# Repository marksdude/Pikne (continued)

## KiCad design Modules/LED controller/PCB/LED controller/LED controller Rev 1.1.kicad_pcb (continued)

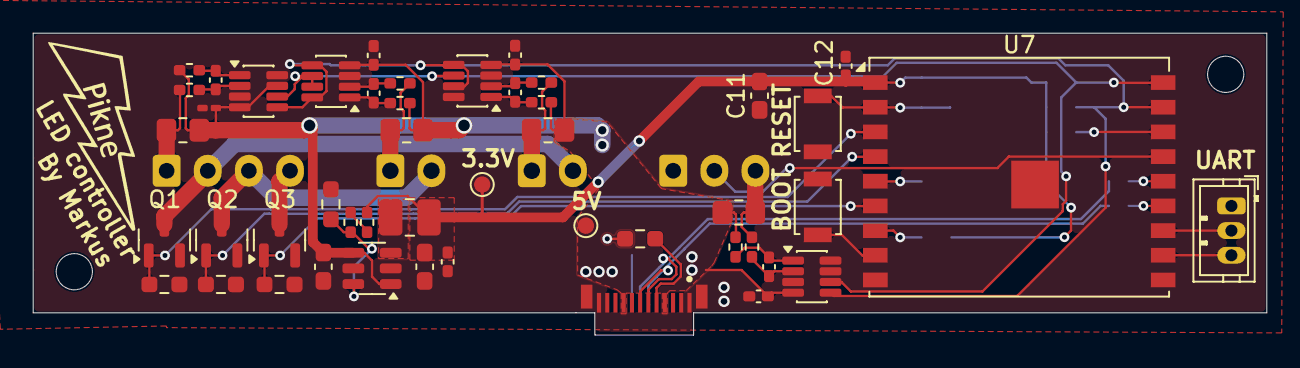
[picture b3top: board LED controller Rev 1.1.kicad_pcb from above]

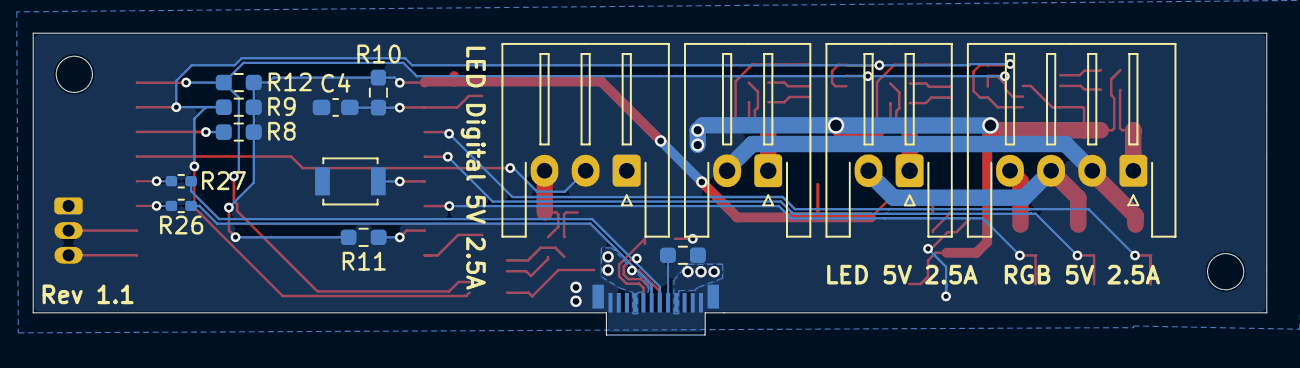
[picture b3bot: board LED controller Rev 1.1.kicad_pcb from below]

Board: 2 copper layers, 75.0 x 18.4 mm, 62 parts (14 on the bottom side), 40 nets.

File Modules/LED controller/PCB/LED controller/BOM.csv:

Id;Designator;Footprint;Quantity;Designation;Price (total) (EUR);Link;Part number
1;C1;C_0603_1608Metric_Pad1.08x0.95mm_HandSolder;1;4.7uf;0,12;https://www.mouser.ee/en/ProductDetail/Samsung-Electro-Mecha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;CL10A475KO8NNNC 
2;C2, C11;C_0603_1608Metric_Pad1.08x0.95mm_HandSolder;2;22uf;0,28;https://www.mouser.ee/en/ProductDetail/Murata-Electronics/GR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;GRM188R60J226MEA0J 
3;C3;C_0402_1005Metric_Pad0.74x0.62mm_HandSolder;1;120pf;0,09;https://www.mouser.ee/en/ProductDetail/Murata-Electronics/GC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;GCM1555C1H121JA16D 
4;C4;C_0603_1608Metric_Pad1.08x0.95mm_HandSolder;1;1uf;0,09;https://www.mouser.ee/en/ProductDetail/Samsung-Electro-Mecha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;CL10B105KQ8NNNC 
5;C5, C6, C7, C9, C10, C12, C13, C14;C_0402_1005Metric_Pad0.74x0.62mm_HandSolder;8;100nF;0,15;https://www.mouser.ee/en/ProductDetail/Murata-Electronics/GR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;GRM155R62A104ME14D 
6;C8;C_0201_0603Metric_Pad0.64x0.40mm_HandSolder;1;100nF;0,09;https://www.mouser.ee/en/ProductDetail/Murata-Electronics/GR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;GRM033R61C104KE18J 
7;;;;;;;
8;J1, J2;JST_XH_S2B-XH-A-1_1x02_P2.50mm_Horizontal;2;LED;0,26;https://www.mouser.ee/en/ProductDetail/JST-Commercial/S2B-XH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;S2B-XH-A-1(LF)(SN) 
9;J3;SAMESKY_UP32-1-C-H-G-BMT-P24;1;UP32-1-C-H-G-BMT-P24;0,78;https://www.mouser.ee/en/ProductDetail/Same-Sky/UP32-1-C-H-G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;UP32-1-C-H-G-BMT-P24 
10;J4;JST_XH_S4B-XH-A-1_1x04_P2.50mm_Horizontal;1;RGB 2A max;0,6;https://www.mouser.ee/ProductDetail/JST-Commercial/S4B-XH-SM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;S4B-XH-SM4-TB(LF)(SN) 
11;J5;JST_XH_S3B-XH-A-1_1x03_P2.50mm_Horizontal;1;RGB 2A max;0,13;https://www.mouser.ee/ProductDetail/JST-Commercial/S3B-XH-A-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;S3B-XH-A-1(LF)(SN) 
12;J7;JST_ZH_B3B-ZR_1x03_P1.50mm_Vertical;1;UART;0,21;https://www.mouser.ee/en/ProductDetail/JST-Commercial/B3B-ZR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;B3B-ZR-3.4(LF)(SN) 
13;L1;L_1008_2520Metric_Pad1.43x2.20mm_HandSolder;1;1uH;0,22;https://www.mouser.ee/ProductDetail/TDK/VLS252012HBX-1R0M-1?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;VLS252012HBX-1R0M-1 
14;Q1, Q2, Q3;SOT-23;3;AO3400A;0,38;https://www.lcsc.com/product-detail/C20917.html;AO3400A
15;R1;R_0402_1005Metric_Pad0.72x0.64mm_HandSolder;1;300k;0,08;https://www.mouser.ee/en/ProductDetail/YAGEO/AC0402FR-07300K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;AC0402FR-07300KL 
16;R2, R6, R7, R8, R10, R11;R_0603_1608Metric_Pad0.98x0.95mm_HandSolder;6;10k;0,09;https://www.mouser.ee/en/ProductDetail/YAGEO/RT0603FRE1310KL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;RT0603FRE1310KL 
17;R3;R_0603_1608Metric_Pad0.98x0.95mm_HandSolder;1;100k;0,09;https://www.mouser.ee/en/ProductDetail/YAGEO/RC0603FR-10100K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;RC0603FR-10100KL 
18;R4, R5;R_0603_1608Metric_Pad0.98x0.95mm_HandSolder;2;5.1k;0,09;https://www.mouser.ee/en/ProductDetail/YAGEO/AC0603JR-075K1L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;AC0603JR-075K1L 
19;R9, R12;R_0603_1608Metric_Pad0.98x0.95mm_HandSolder;2;4.7k;0,09;https://www.mouser.ee/en/ProductDetail/YAGEO/AC0603JR-074K7L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;AC0603JR-074K7L 
20;R13, R14, R17, R18, R20, R21, R23, R24;R_0402_1005Metric_Pad0.72x0.64mm_HandSolder;8;10 Ohm;0,08;https://www.mouser.ee/en/ProductDetail/Bourns/CR0402-FX-10R0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;CR0402-FX-10R0GLF 
21;R15, R16, R19, R22;R_0805_2012Metric_Pad1.20x1.40mm_HandSolder;4;20m;1,17;https://www.mouser.ee/en/ProductDetail/Eaton-Electronics/MFS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;MFSA0805R0200FIM 
22;R25;R_0402_1005Metric_Pad0.72x0.64mm_HandSolder;1;150k;0,09;https://www.mouser.ee/en/ProductDetail/YAGEO/RC0402FR-07150K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;RC0402FR-07150KP 
23;R26, R27;R_0402_1005Metric_Pad0.72x0.64mm_HandSolder;2;22 Ohm;0,08;https://www.mouser.ee/en/ProductDetail/Bourns/CR0402-FX-22R0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;CR0402-FX-22R0GLF 
24;SW1, SW2, SW3;SW_SPST_B3U-1000P;3;;2,81;https://www.mouser.ee/en/ProductDetail/Omron-Electronics/B3U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;B3U-1000P 
25;;;;;;;
26;;;;;;;
27;TP1;TestPoint_Pad_D1.0mm;1;3.3V;;;
28;TP2;TestPoint_Pad_D1.0mm;1;5V;;;
29;U1, U2, U3, U5;SOT-23-8;4;INA219AxDCN;7,28;https://www.mouser.ee/ProductDetail/Texas-Instruments/INA219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;INA219AIDCNR 
30;U4;SOT-23-6;1;TPS62A02APDDC;0,21;https://www.mouser.ee/ProductDetail/Texas-Instruments/TPS62A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;TPS62A02APDDCR 
31;U7;ESP32-C3-WROOM-02U;1;ESP32-C3-WROOM-02;3,19;https://www.mouser.ee/en/ProductDetail/Espressif-Systems/ESP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;ESP32-C3-WROOM-02U-N4 
;;;;Total (EUR);18,75;;
;;;;Total (USD);21,75;;

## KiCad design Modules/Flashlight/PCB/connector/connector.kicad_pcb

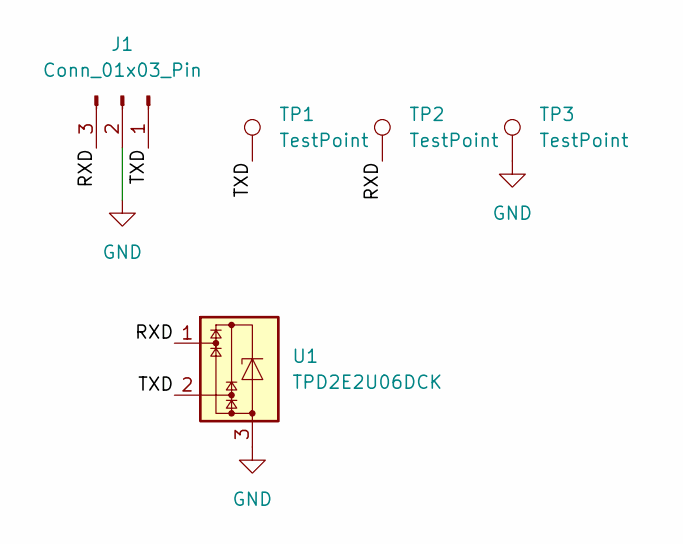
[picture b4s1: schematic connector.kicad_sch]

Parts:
J1: Conn_01x03_Pin; Pogo 3 Pin
TP1, TP2, TP3: TestPoint; TestPoint_Pad_D1.0mm
U1: TPD2E2U06DCK; SOT-323_SC-70

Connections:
/RXD: J1.3, TP2.1 (1_1), U1.1
/TXD: J1.1, TP1.1 (1_1), U1.2
GND: J1.2, TP3.1 (1_1), U1.3

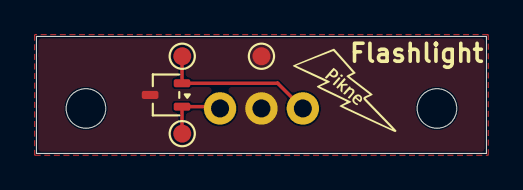
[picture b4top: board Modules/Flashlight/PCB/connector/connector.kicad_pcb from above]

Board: 2 copper layers, 25.0 x 6.5 mm, 5 parts (1 on the bottom side), 3 nets.

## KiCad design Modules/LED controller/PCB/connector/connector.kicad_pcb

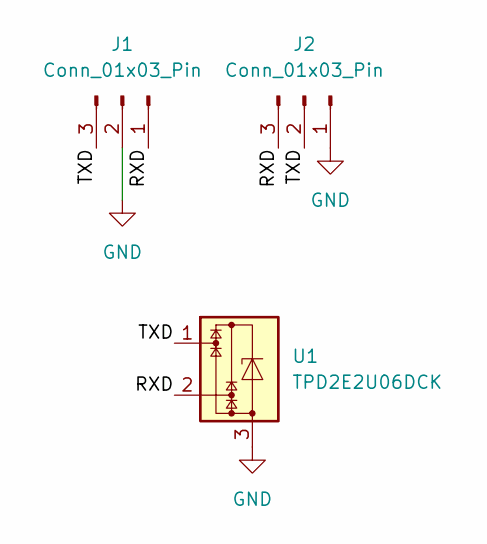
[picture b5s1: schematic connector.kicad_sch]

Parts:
J1: Conn_01x03_Pin; Pogo 3 Pin
J2: Conn_01x03_Pin; JST_ZH_S3B-ZR-SM4A-TF_1x03-1MP_P1.50mm_Horizontal
U1: TPD2E2U06DCK; SOT-323_SC-70

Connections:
/RXD: J1.1, J2.3, U1.2
/TXD: J1.3, J2.2, U1.1
GND: J1.2, J2.1, U1.3

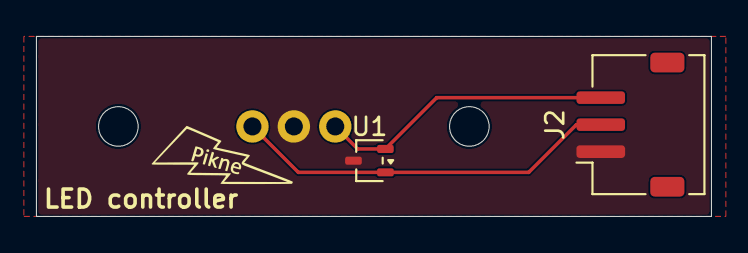
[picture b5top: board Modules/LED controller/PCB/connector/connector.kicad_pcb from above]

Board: 2 copper layers, 37.5 x 10.0 mm, 3 parts (1 on the bottom side), 3 nets.

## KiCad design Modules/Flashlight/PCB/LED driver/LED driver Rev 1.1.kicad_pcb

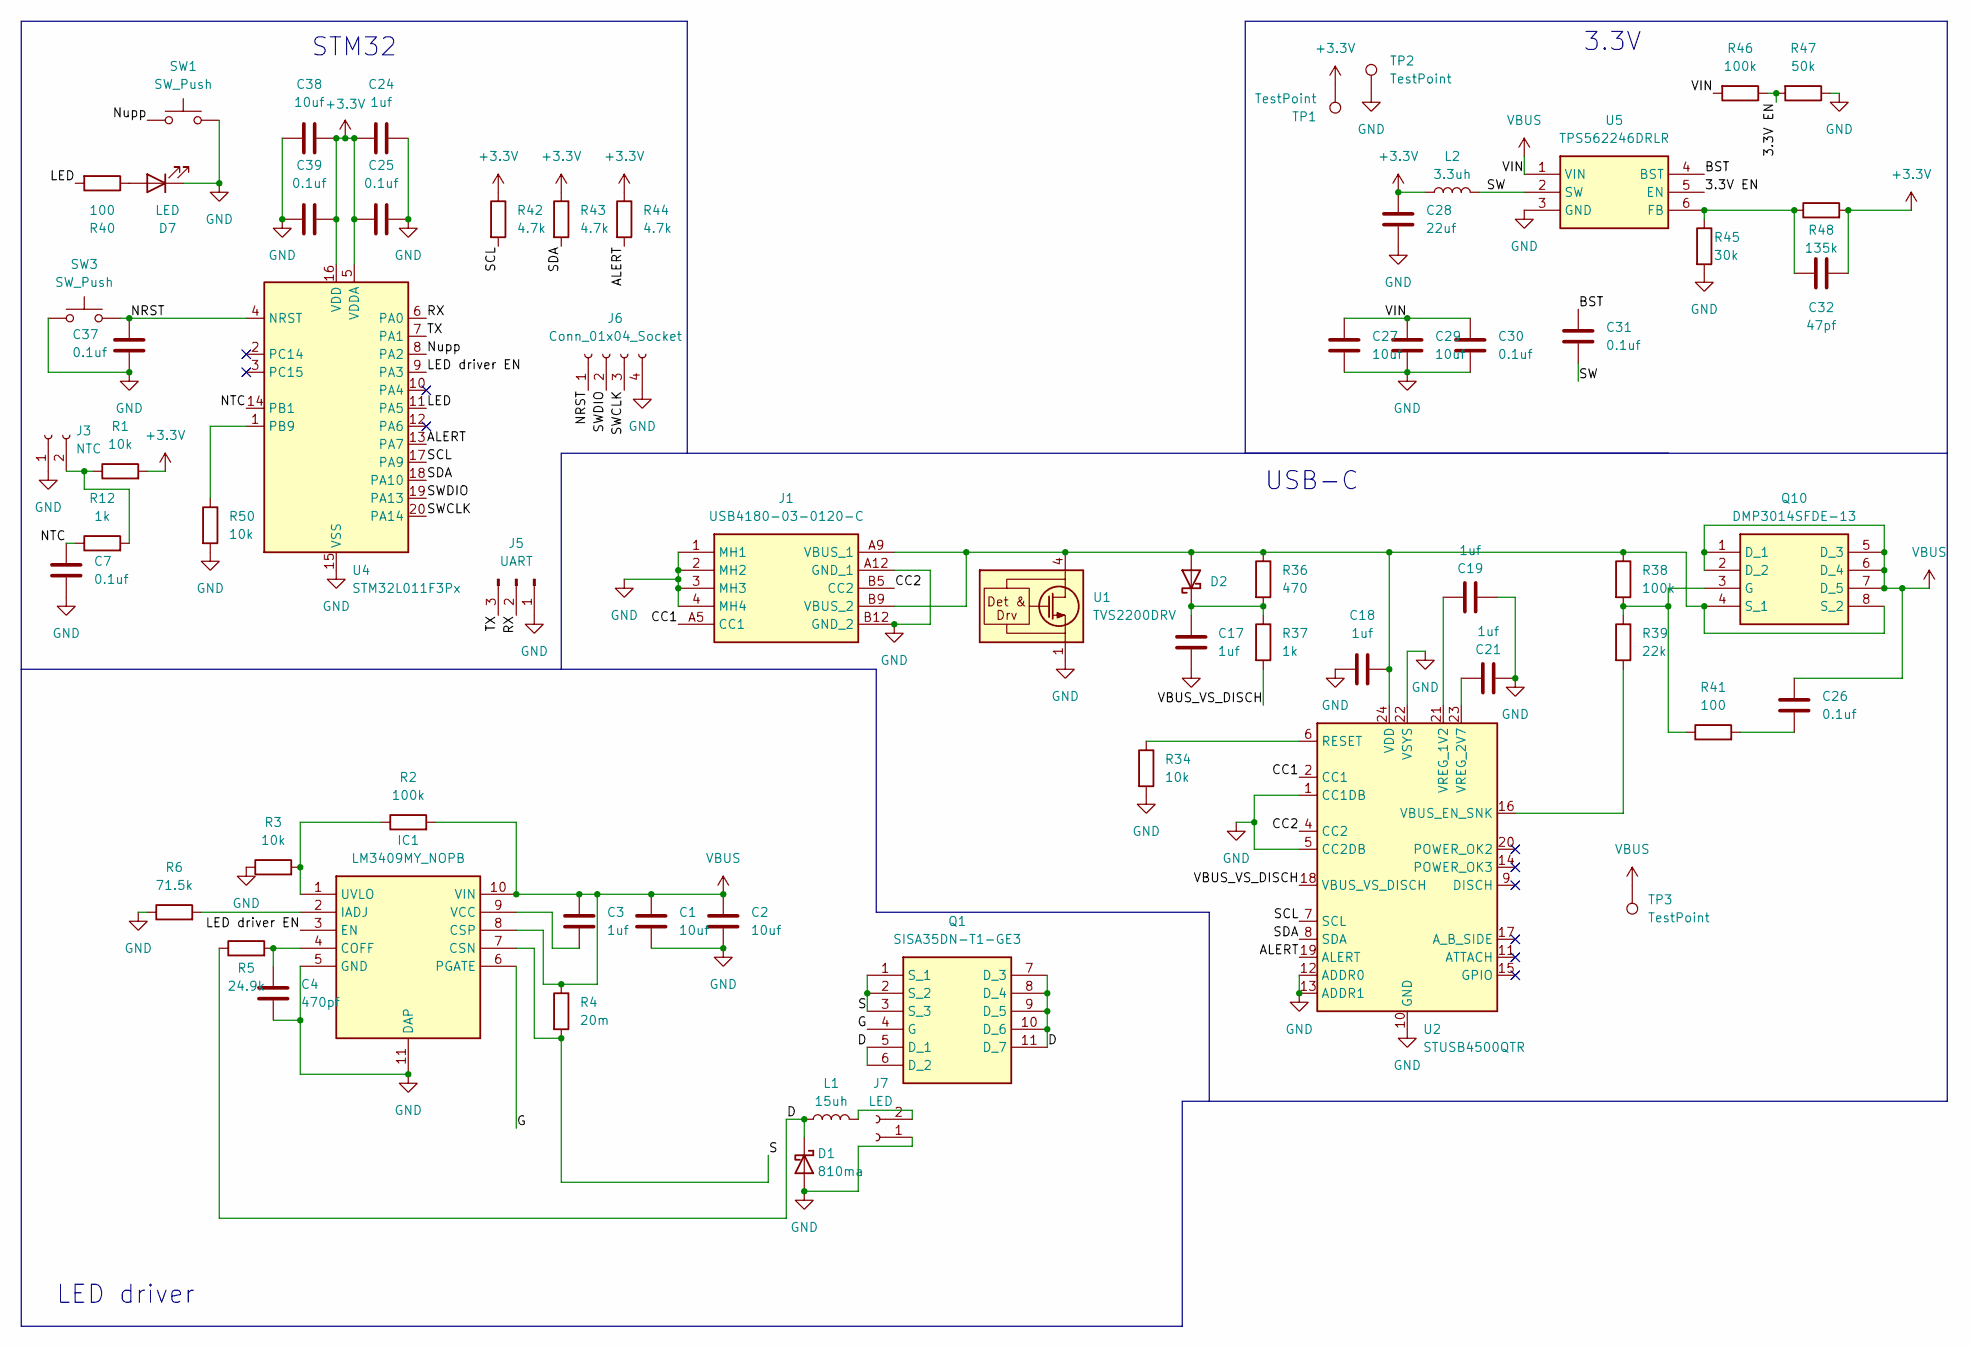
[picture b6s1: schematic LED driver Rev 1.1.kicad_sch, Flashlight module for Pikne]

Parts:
C1, C2: 10uf; C_1206_3216Metric
C3, C19, C21: 1uf; C_0402_1005Metric
C4: 470pf; C_0402_1005Metric
C7, C25, C26, C30, C31, C37, C39: 0.1uf; C_0402_1005Metric
C17, C18, C24: 1uf; C_0603_1608Metric
C27, C29, C38: 10uf; C_0603_1608Metric
C28: 22uf; C_0805_2012Metric
C32: 47pf; R_0402_1005Metric
D1: 810ma; D_SMF
D2: D_Schottky; D_SOD-323_HandSoldering
D7: LED; LED_0603_1608Metric
IC1: LM3409MY_NOPB; SOP50P490X109-11N; Mouser Part Number 926-LM3409MY/NOPB
J1: USB4180-03-0120-C; USB4180030120C; Mouser Part Number 640-USB4180-03-0120C
J3: NTC; JST_ZH_B2B-ZR_1x02_P1.50mm_Vertical
J5: UART; JST_ZH_B3B-ZR_1x03_P1.50mm_Vertical
J6: Conn_01x04_Socket; JST_ZH_B4B-ZR_1x04_P1.50mm_Vertical
J7: LED; JST_XH_S2B-XH-A-1_1x02_P2.50mm_Horizontal
L1: 15uh; L_Bourns_SRP1038C_10.0x10.0mm
L2: 3.3uh; INDC3225X120N
Q1: SISA35DN-T1-GE3; SISA35DNT1GE3; Mouser Part Number 78-SISA35DN-T1-GE3
Q10: DMP3014SFDE-13; DMP1022UFDEQ7; Manufacturer_Part_Number DMP3014SFDE-13
R1, R3, R34: 10k; R_0603_1608Metric
R2, R38: 100k; R_0603_1608Metric
R4: 20m; R_1206_3216Metric
R5: 24.9k; R_0603_1608Metric
R6: 71.5k; R_0603_1608Metric
R12: 1k; R_0402_1005Metric
R36: 470; R_0603_1608Metric
R37: 1k; R_0603_1608Metric
R39: 22k; R_0603_1608Metric
R40, R41: 100; R_0402_1005Metric
R42, R43, R44: 4.7k; R_0603_1608Metric
R45: 30k; R_0402_1005Metric
R46: 100k; R_0402_1005Metric
R47: 50k; R_0402_1005Metric
R48: 135k; R_0402_1005Metric
R50: 10k; R_0402_1005Metric
SW1: SW_Push; SW_Tactile_SPST_Angled_PTS645Vx39-2LFS
SW3: SW_Push; SW_SPST_B3U-1000P
TP1, TP2, TP3: TestPoint; TestPoint_Pad_D1.0mm
U1: TVS2200DRV; WSON-6-1EP_2x2mm_P0.65mm_EP1x1.6mm
U2: STUSB4500QTR; QFN-24-1EP_4x4mm_P0.5mm_EP2.7x2.7mm
U4: STM32L011F3Px; TSSOP-20_4.4x6.5mm_P0.65mm
U5: TPS562246DRLR; SOTFL50P160X60-6N; Mouser Part Number 595-TPS562246DRLR

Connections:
+3.3V: C24.1, C25.1, C28.1, C32.1, C38.2, C39.2, L2.1, R1.2, R42.1, R43.1, R44.1, R48.2, TP1.1 (1_1), U4.5 (VDDA), U4.16 (VDD)
/3.3V EN: R46.1, R47.2, U5.5 (EN)
/ALERT: R44.2, U2.19 (ALERT), U4.13 (PA7)
/BST: C31.2, U5.4 (BST)
/CC1: J1.A5 (CC1), U2.2 (CC1)
/CC2: J1.B5 (CC2), U2.4 (CC2)
/D: D1.1 (K), L1.1, Q1.5 (D_1), Q1.6 (D_2), Q1.7 (D_3), Q1.8 (D_4), Q1.9 (D_5), Q1.10 (D_6), Q1.11 (D_7), R5.1
/G: IC1.6 (PGATE), Q1.4 (G)
/LED: R40.2, U4.11 (PA5)
/LED driver EN: IC1.3 (EN), U4.9 (PA3)
/NRST: C37.2, J6.1, SW3.2, U4.4 (NRST)
/NTC: C7.1, R12.1, U4.14 (PB1)
/Nupp: SW1.1, U4.8 (PA2)
/RX: J5.2, U4.6 (PA0)
/S: IC1.7 (CSN), Q1.1 (S_1), Q1.2 (S_2), Q1.3 (S_3), R4.2
/SCL: R42.2, U2.7 (SCL), U4.17 (PA9)
/SDA: R43.2, U2.8 (SDA), U4.18 (PA10)
/SW: C31.1, L2.2, U5.2 (SW)
/SWCLK: J6.3, U4.20 (PA14)
/SWDIO: J6.2, U4.19 (PA13)
/TX: J5.3, U4.7 (PA1)
/VBUS_VS_DISCH: R37.2, U2.18 (VBUS_VS_DISCH)
GND: C1.2, C2.2, C4.2, C7.2, C17.1, C18.1, C19.1, C21.1, C24.2, C25.2, C27.2, C28.2, C29.2, C30.2, C37.1, C38.1, C39.1, D1.2 (A), D7.1 (K), IC1.5 (GND), IC1.11 (DAP), J1.1 (MH1), J1.2 (MH2), J1.3 (MH3), J1.4 (MH4), J1.A12 (GND_1), J1.B12 (GND_2), J3.1, J5.1, J6.4, J7.1, R3.1, R6.1, R34.2, R45.2, R47.1, R50.2, SW1.2, SW3.1, TP2.1 (1_1), U1.1 (GND), U1.2 (GND), U1.3 (GND), U1.7 (GND), U2.1 (CC1DB), U2.5 (CC2DB), U2.10 (GND), U2.12 (ADDR0), U2.13 (ADDR1), U2.22 (VSYS), U2.25 (GND), U4.15 (VSS), U5.3 (GND)
unnamed: C26.2, R41.2
unnamed: C18.2, D2.2 (A), J1.A9 (VBUS_1), J1.B9 (VBUS_2), Q10.4 (S_1), Q10.8 (S_2), R36.1, R38.1, U1.4 (IN), U1.5 (IN), U1.6 (IN), U2.24 (VDD)
unnamed: C17.2, D2.1 (K), R36.2, R37.1
unnamed: D7.2 (A), R40.1
unnamed: C4.1, IC1.4 (COFF), R5.2
unnamed: IC1.2 (IADJ), R6.2
unnamed: IC1.1 (UVLO), R2.1, R3.2
unnamed: C3.2, IC1.9 (VCC)
unnamed: J3.2, R1.1, R12.2
unnamed: J7.2, L1.2
unnamed: Q10.3 (G), R38.2, R39.1, R41.1
unnamed: R34.1, U2.6 (RESET)
unnamed: R39.2, U2.16 (VBUS_EN_SNK)
unnamed: C19.2, U2.21 (VREG_1V2)
unnamed: C21.2, U2.23 (VREG_2V7)
unnamed: R50.1, U4.1 (PB9)
unnamed: C32.2, R45.1, R48.1, U5.6 (FB)
VBUS: C1.1, C2.1, C3.1, C26.1, C27.1, C29.1, C30.1, IC1.8 (CSP), IC1.10 (VIN), Q10.1 (D_1), Q10.2 (D_2), Q10.5 (D_3), Q10.6 (D_4), Q10.7 (D_5), R2.2, R4.1, R46.2, TP3.1 (1_1), U5.1 (VIN)

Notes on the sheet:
3.3V
LED driver
USB-C
STM32

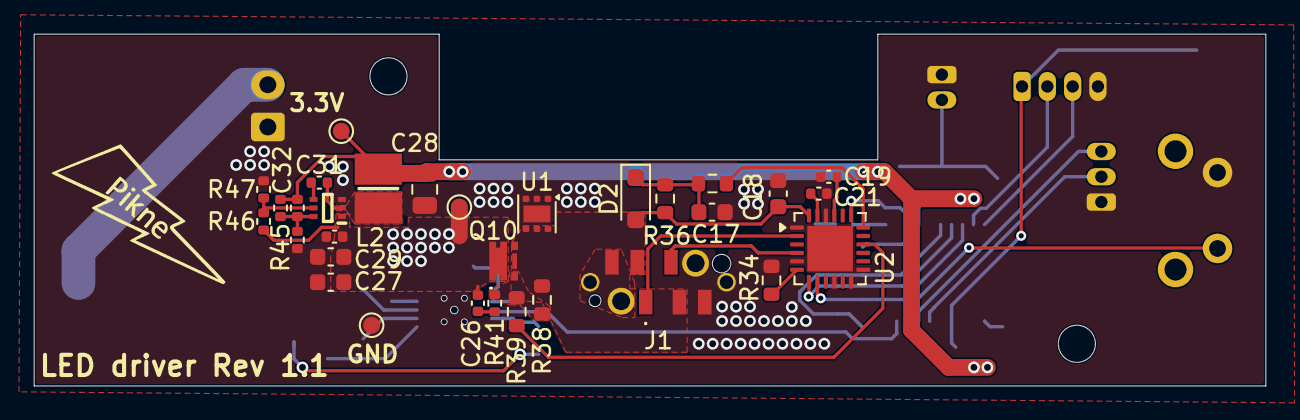
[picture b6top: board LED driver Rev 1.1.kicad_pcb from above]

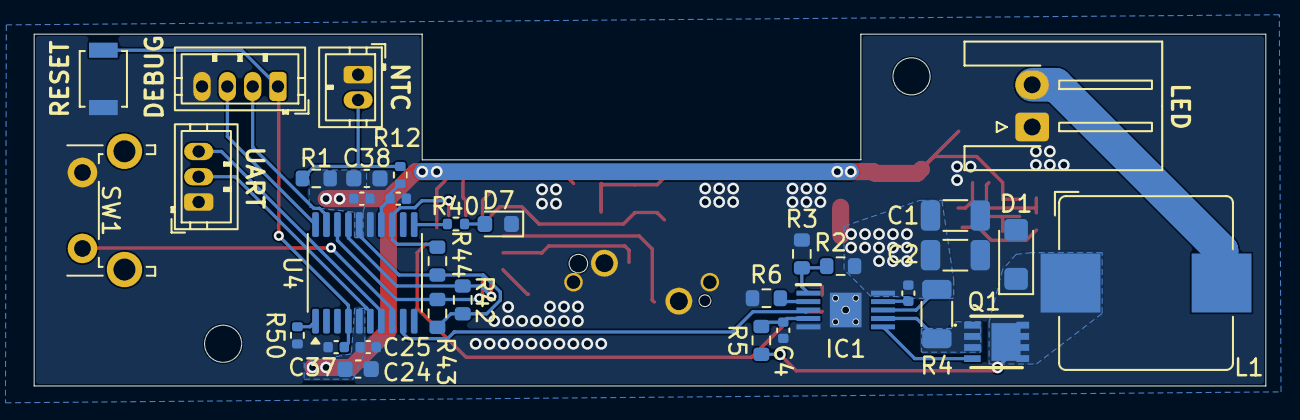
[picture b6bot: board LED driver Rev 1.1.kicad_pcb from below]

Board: 2 copper layers, 73.0 x 20.8 mm, 65 parts (34 on the bottom side), 41 nets.

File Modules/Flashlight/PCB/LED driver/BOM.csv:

Id;Designator;Footprint;Quantity;Designation;Price (total) (EUR);Link;Part number;alternative
1;C1, C2, C27, C29;C_1206_3216Metric;4;10uf;1;https://www.mouser.ee/en/ProductDetail/TAIYO-YUDEN/MSAST31LS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;MSAST31LSB5106KTNA01 ;
2;C3, C19, C21;C_0402_1005Metric;3;1uf;0,26;https://www.mouser.ee/en/ProductDetail/Murata-Electronics/GR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;GRM155R61E105MA12D ;
3;C4;C_0402_1005Metric;1;470pf;0,09;https://www.mouser.ee/en/ProductDetail/Murata-Electronics/GC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;GCM155L81H471KA37D ;
4;C5;C_0603_1608Metric;1;4.7uf;0,27;https://www.mouser.ee/en/ProductDetail/Murata-Electronics/GR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;GRM188R6YA475ME15D ;
5;C7, C25, C26, C30, C31, C37, C39;C_0402_1005Metric;7;0.1uf;0,15;https://www.mouser.ee/en/ProductDetail/Murata-Electronics/GR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;GRM155R62A104ME14D ;
6;C17, C18, C24;C_0603_1608Metric;3;1uf;0,19;https://www.mouser.ee/en/ProductDetail/Samsung-Electro-Mecha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;CL10A105KA8NNND ;
7;C38;C_0603_1608Metric;1;10uf;0,09;https://www.mouser.ee/en/ProductDetail/Samsung-Electro-Mecha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;CL10A105KA8NFNC ;
8;C28;C_0805_2012Metric;1;22uf;0,15;https://www.mouser.ee/en/ProductDetail/Samsung-Electro-Mecha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;CL21A226MQQNNNE ;
9;C32;R_0402_1005Metric;1;47pf;0,09;https://www.mouser.ee/en/ProductDetail/Murata-Electronics/GR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;GRM1555C1H470GA01D ;
10;D1;D_SMF;1;1.2A;0,4;https://www.mouser.ee/en/ProductDetail/Vishay-Semiconductors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;V3FL45-M3/H ;
11;D2;D_SOD-323_HandSoldering;1;D_Schottky;0,13;https://www.mouser.ee/en/ProductDetail/onsemi/NSR0530HT1G?qs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;NSR0530HT1G ;
12;D3;SOT-323_SC-70;1;ESDA25W;0,36;https://www.mouser.ee/en/ProductDetail/STMicroelectronics/ES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;ESDA25W ;
13;D7;LED_0603_1608Metric;1;LED;0,28;https://www.mouser.ee/en/ProductDetail/ams-OSRAM/KT-EELP41.1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;KT EELP41.12-S2U1-25-2X4X-5-R18 ;
14;IC1;SOP50P490X109-11N;1;LM3409MY_NOPB;2,41;https://www.mouser.ee/en/ProductDetail/Texas-Instruments/LM3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;LM3409HVMYX/NOPB ;
15;J1;USB4180030120C;1;USB4180-03-0120-C;0,87;https://www.mouser.ee/en/ProductDetail/GCT/USB4180-03-0120-C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;USB4180-03-0120-C ;
16;J3;JST_ZH_B2B-ZR_1x02_P1.50mm_Vertical;1;NTC;0,1;https://www.mouser.ee/en/ProductDetail/JST-Commercial/B2B-ZR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;B2B-ZR(LF)(SN) ;
17;J5;JST_ZH_B3B-ZR_1x03_P1.50mm_Vertical;1;UART;0,21;https://www.mouser.ee/en/ProductDetail/JST-Commercial/B3B-ZR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;B3B-ZR-3.4(LF)(SN) ;
18;J6;JST_ZH_B4B-ZR_1x04_P1.50mm_Vertical;1;Conn_01x04_Socket;0,21;https://www.mouser.ee/en/ProductDetail/JST-Commercial/B4B-ZR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;B4B-ZR-3.4(LF)(SN) ;
19;J7;JST_XH_S2B-XH-A-1_1x02_P2.50mm_Horizontal;1;LED;0,13;https://www.mouser.ee/en/ProductDetail/JST-Commercial/S2B-XH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;S2B-XH-A-1(LF)(SN) ;
20;L1;L_Bourns_SRP1038C_10.0x10.0mm;1;15uh;0,84;https://www.mouser.ee/en/ProductDetail/Bourns/SRP1038CC-150M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;SRP1038CC-150M ;SRP1038C-150M 
21;L2;INDC3225X120N;1;3.3uh;0,34;https://www.mouser.ee/en/ProductDetail/Bourns/SRP3212A-3R3M?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;SRP3212A-3R3M ;
22;Q1;SISA35DNT1GE3;1;SISA35DN-T1-GE3;0,67;https://www.mouser.ee/en/ProductDetail/Vishay-Semiconductors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;SISA35DN-T1-GE3 ;
23;Q10;DMP1022UFDEQ7;1;DMP3014SFDE-13;0,43;https://www.mouser.ee/en/ProductDetail/Diodes-Incorporated/D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;DMP3014SFDE-13 ;
24;R1, R3;R_0603_1608Metric;2;10k;0,09;https://www.mouser.ee/en/ProductDetail/YAGEO/RT0603FRE1310KL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;RT0603FRE1310KL ;
25;R2, R38;R_0603_1608Metric;2;100k;0,12;https://www.mouser.ee/en/ProductDetail/YAGEO/RC0603FR-10100K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;RC0603FR-10100KL ;
26;R4;R_1206_3216Metric;1;20m;0,32;https://www.mouser.ee/en/ProductDetail/Eaton-Electronics/MFS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;MFSA1206R0200FCM ;
27;R5;R_0603_1608Metric;1;24.9k;0,09;https://www.mouser.ee/en/ProductDetail/SEI-Stackpole/RNCP060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;RNCP0603FTD24K9 ;
28;R6;R_0603_1608Metric;1;71.5k;0,09;https://www.mouser.ee/en/ProductDetail/Vishay/CRCW060371K5FK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;CRCW060371K5FKEA ;
29;R7, R9, R46;R_0402_1005Metric;3;100k;0,09;https://www.mouser.ee/en/ProductDetail/YAGEO/RC0402FR-07100K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;RC0402FR-07100KL ;
30;R12;R_0402_1005Metric;1;1k;0,09;https://www.mouser.ee/en/ProductDetail/YAGEO/RC0402FR-101KL?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;RC0402FR-101KL ;
31;R34, R50;R_0402_1005Metric;2;10k;0,09;https://www.mouser.ee/en/ProductDetail/YAGEO/RC0402FR-0710KL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;RC0402FR-0710KL ;
32;R36;R_0603_1608Metric;1;470;0,09;https://www.mouser.ee/en/ProductDetail/YAGEO/RC0603JR-07470R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;RC0603JR-07470RL ;
33;R37;R_0603_1608Metric;1;1k;0,09;https://www.mouser.ee/en/ProductDetail/YAGEO/AC0603JR-131KL?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;AC0603JR-131KL ;
34;R39;R_0603_1608Metric;1;22k;0,09;https://www.mouser.ee/en/ProductDetail/Walsin/WR06X223-JTL?q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;WR06X223 JTL ;
35;R41;R_0402_1005Metric;1;100;0,08;https://www.mouser.ee/en/ProductDetail/YAGEO/AC0402FR-13100R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;AC0402FR-13100RL ;
36;R42, R43, R44;R_0603_1608Metric;3;4.7k;0,09;https://www.mouser.ee/en/ProductDetail/YAGEO/AC0603JR-074K7L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;AC0603JR-074K7L ;
37;R45;R_0402_1005Metric;1;30k;0,08;https://www.mouser.ee/en/ProductDetail/Walsin/WR04X3002FTL?q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;WR04X3002FTL ;
38;R47;R_0402_1005Metric;1;50k;0,09;https://www.mouser.ee/en/ProductDetail/SEI-Stackpole/RNCF040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;RNCF0402DKE50K0 ;
39;R48;R_0402_1005Metric;1;135k;0,15;https://www.mouser.ee/en/ProductDetail/KOA-Speer/RN73H1ETTP1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;RN73H1ETTP1353F50 ;
40;SW1;SW_Tactile_SPST_Angled_PTS645Vx39-2LFS;1;SW_Push;0,3;https://www.mouser.ee/en/ProductDetail/CK/PTS645VM39-2-LFS?q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;PTS645VM39-2 LFS ;
41;SW3;SW_SPST_B3U-1000P;1;SW_Push;0,94;https://www.mouser.ee/en/ProductDetail/Omron-Electronics/B3U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;B3U-1000P ;
42;TP1, TP2, TP3;TestPoint_Pad_D1.0mm;3;TestPoint;;;;
43;U1;WSON-6-1EP_2x2mm_P0.65mm_EP1x1.6mm;1;TVS2200DRV;0,93;https://www.mouser.ee/en/ProductDetail/Texas-Instruments/TVS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;TVS2200DRVR ;
44;U2;QFN-24-1EP_4x4mm_P0.5mm_EP2.7x2.7mm;1;STUSB4500QTR;0,91;https://www.mouser.ee/en/ProductDetail/STMicroelectronics/ST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;STUSB4500QTR ;
45;U4;TSSOP-20_4.4x6.5mm_P0.65mm;1;STM32L011F3Px;1,58;https://www.mouser.ee/en/ProductDetail/STMicroelectronics/ST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;STM32L011F3P6 ;
46;U5;SOTFL50P160X60-6N;1;TPS562246DRLR;0,27;https://www.mouser.ee/en/ProductDetail/Texas-Instruments/TPS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;TPS562246DRLR ;
47;R40;R_0402_1005Metric;1;160;0,07;https://www.mouser.ee/en/ProductDetail/YAGEO/RC0402JR-07160R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;RC0402JR-07160RL ;
;;;;Total (EUR);16,41;;;
;;;;Total (USD);19,04;;;

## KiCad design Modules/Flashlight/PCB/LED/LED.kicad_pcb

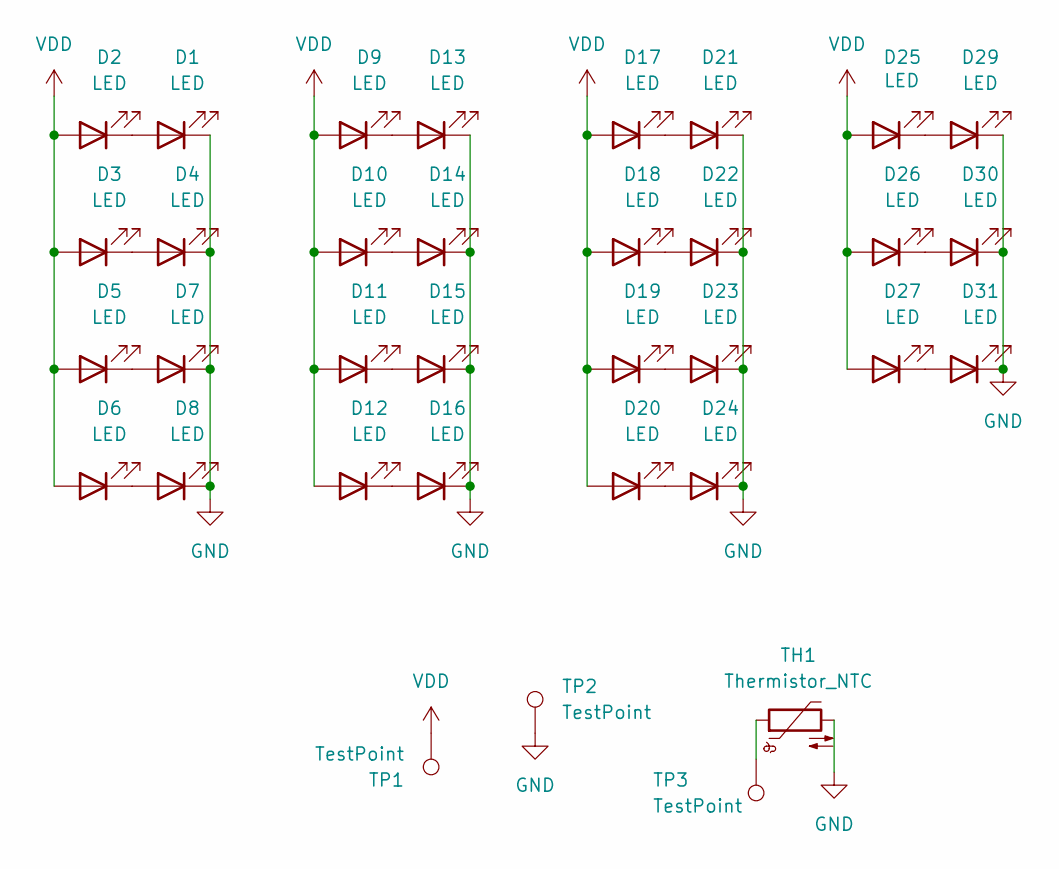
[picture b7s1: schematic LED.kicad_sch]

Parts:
D1, D2, D3, D4, D5, D6, D7, D8, D9, D10, D11, D12, D13, D14, D15, D16, D17, D18, D19, D20, D21, D22, D23, D24, D25, D26, D27, D29, D30, D31: LED; Q9LR37
TH1: Thermistor_NTC; R_0402_1005Metric
TP1, TP2: TestPoint; TestPoint_Pad_D3.0mm
TP3: TestPoint; TestPoint_Pad_D1.5mm

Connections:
GND: D1.1 (K), D4.1 (K), D7.1 (K), D8.1 (K), D13.1 (K), D14.1 (K), D15.1 (K), D16.1 (K), D21.1 (K), D22.1 (K), D23.1 (K), D24.1 (K), D29.1 (K), D30.1 (K), D31.1 (K), TH1.2, TP2.1 (1_1)
unnamed: D1.2 (A), D2.1 (K)
unnamed: D3.1 (K), D4.2 (A)
unnamed: D5.1 (K), D7.2 (A)
unnamed: D6.1 (K), D8.2 (A)
unnamed: D10.1 (K), D14.2 (A)
unnamed: D11.1 (K), D15.2 (A)
unnamed: D12.1 (K), D16.2 (A)
unnamed: D9.1 (K), D13.2 (A)
unnamed: D17.1 (K), D21.2 (A)
unnamed: D18.1 (K), D22.2 (A)
unnamed: D19.1 (K), D23.2 (A)
unnamed: D20.1 (K), D24.2 (A)
unnamed: D25.1 (K), D29.2 (A)
unnamed: D26.1 (K), D30.2 (A)
unnamed: D27.1 (K), D31.2 (A)
unnamed: TH1.1, TP3.1 (1_1)
VDD: D2.2 (A), D3.2 (A), D5.2 (A), D6.2 (A), D9.2 (A), D10.2 (A), D11.2 (A), D12.2 (A), D17.2 (A), D18.2 (A), D19.2 (A), D20.2 (A), D25.2 (A), D26.2 (A), D27.2 (A), TP1.1 (1_1)

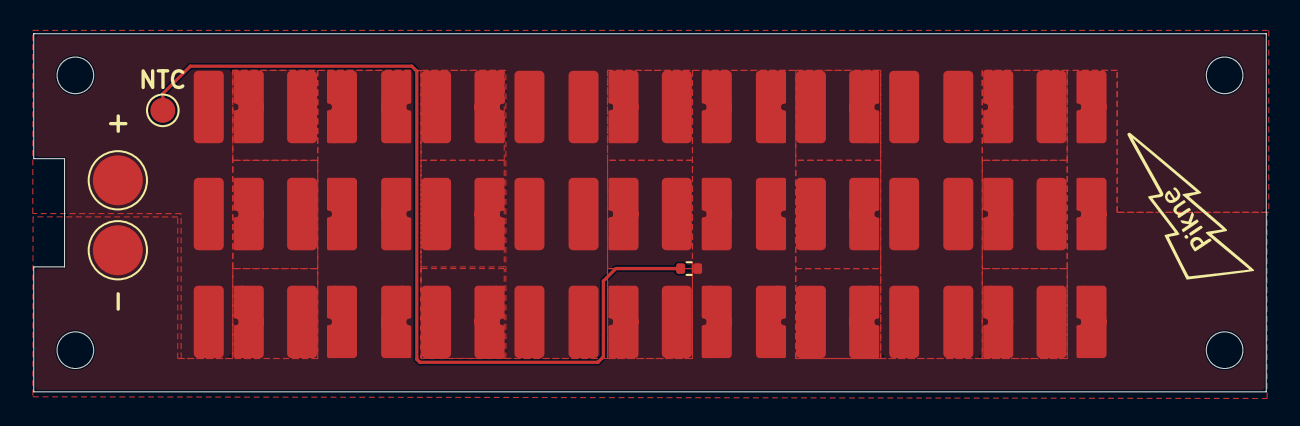
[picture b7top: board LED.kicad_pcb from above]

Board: 2 copper layers, 74.0 x 21.5 mm, 34 parts (0 on the bottom side), 18 nets.

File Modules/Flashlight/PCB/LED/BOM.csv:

Id;Designator;Footprint;Quantity;Designation;Price (total) (EUR);Link;Part number
1;D1, D2, D3, D4, D5, D6, D7, D8, D9, D10, D11, D12, D13, D14, D15, D16, D17, D18, D19, D20, D21, D22, D23, D24, D25, D26, D27, D29, D30, D31;Q9LR37;30;LED;23,22;https://www.mouser.ee/en/ProductDetail/ams-OSRAM/GW-Q9LR37EM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;GW Q9LR37EMM2MF531 
2;TH1;R_0402_1005Metric;1;Thermistor_NTC;0,09;https://www.mouser.ee/en/ProductDetail/Murata-Electronics/NC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;NCU15XH103J6SRC 
;;;;Total (EUR);23,31;;
;;;;Total (USD);27,07;;
